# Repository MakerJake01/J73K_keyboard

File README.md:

# J73K_keyboard
a 15*5 ortholinear keyboard using an atmega32a and usb c. V1.1 
with a 3d printed case and all the parts at the top of the pcb. 

Photo [album](https://imgur.com/a/fLlZRP2)
[sound test](https://www.youtube.com/watch?v=JekZULcJLEQ)

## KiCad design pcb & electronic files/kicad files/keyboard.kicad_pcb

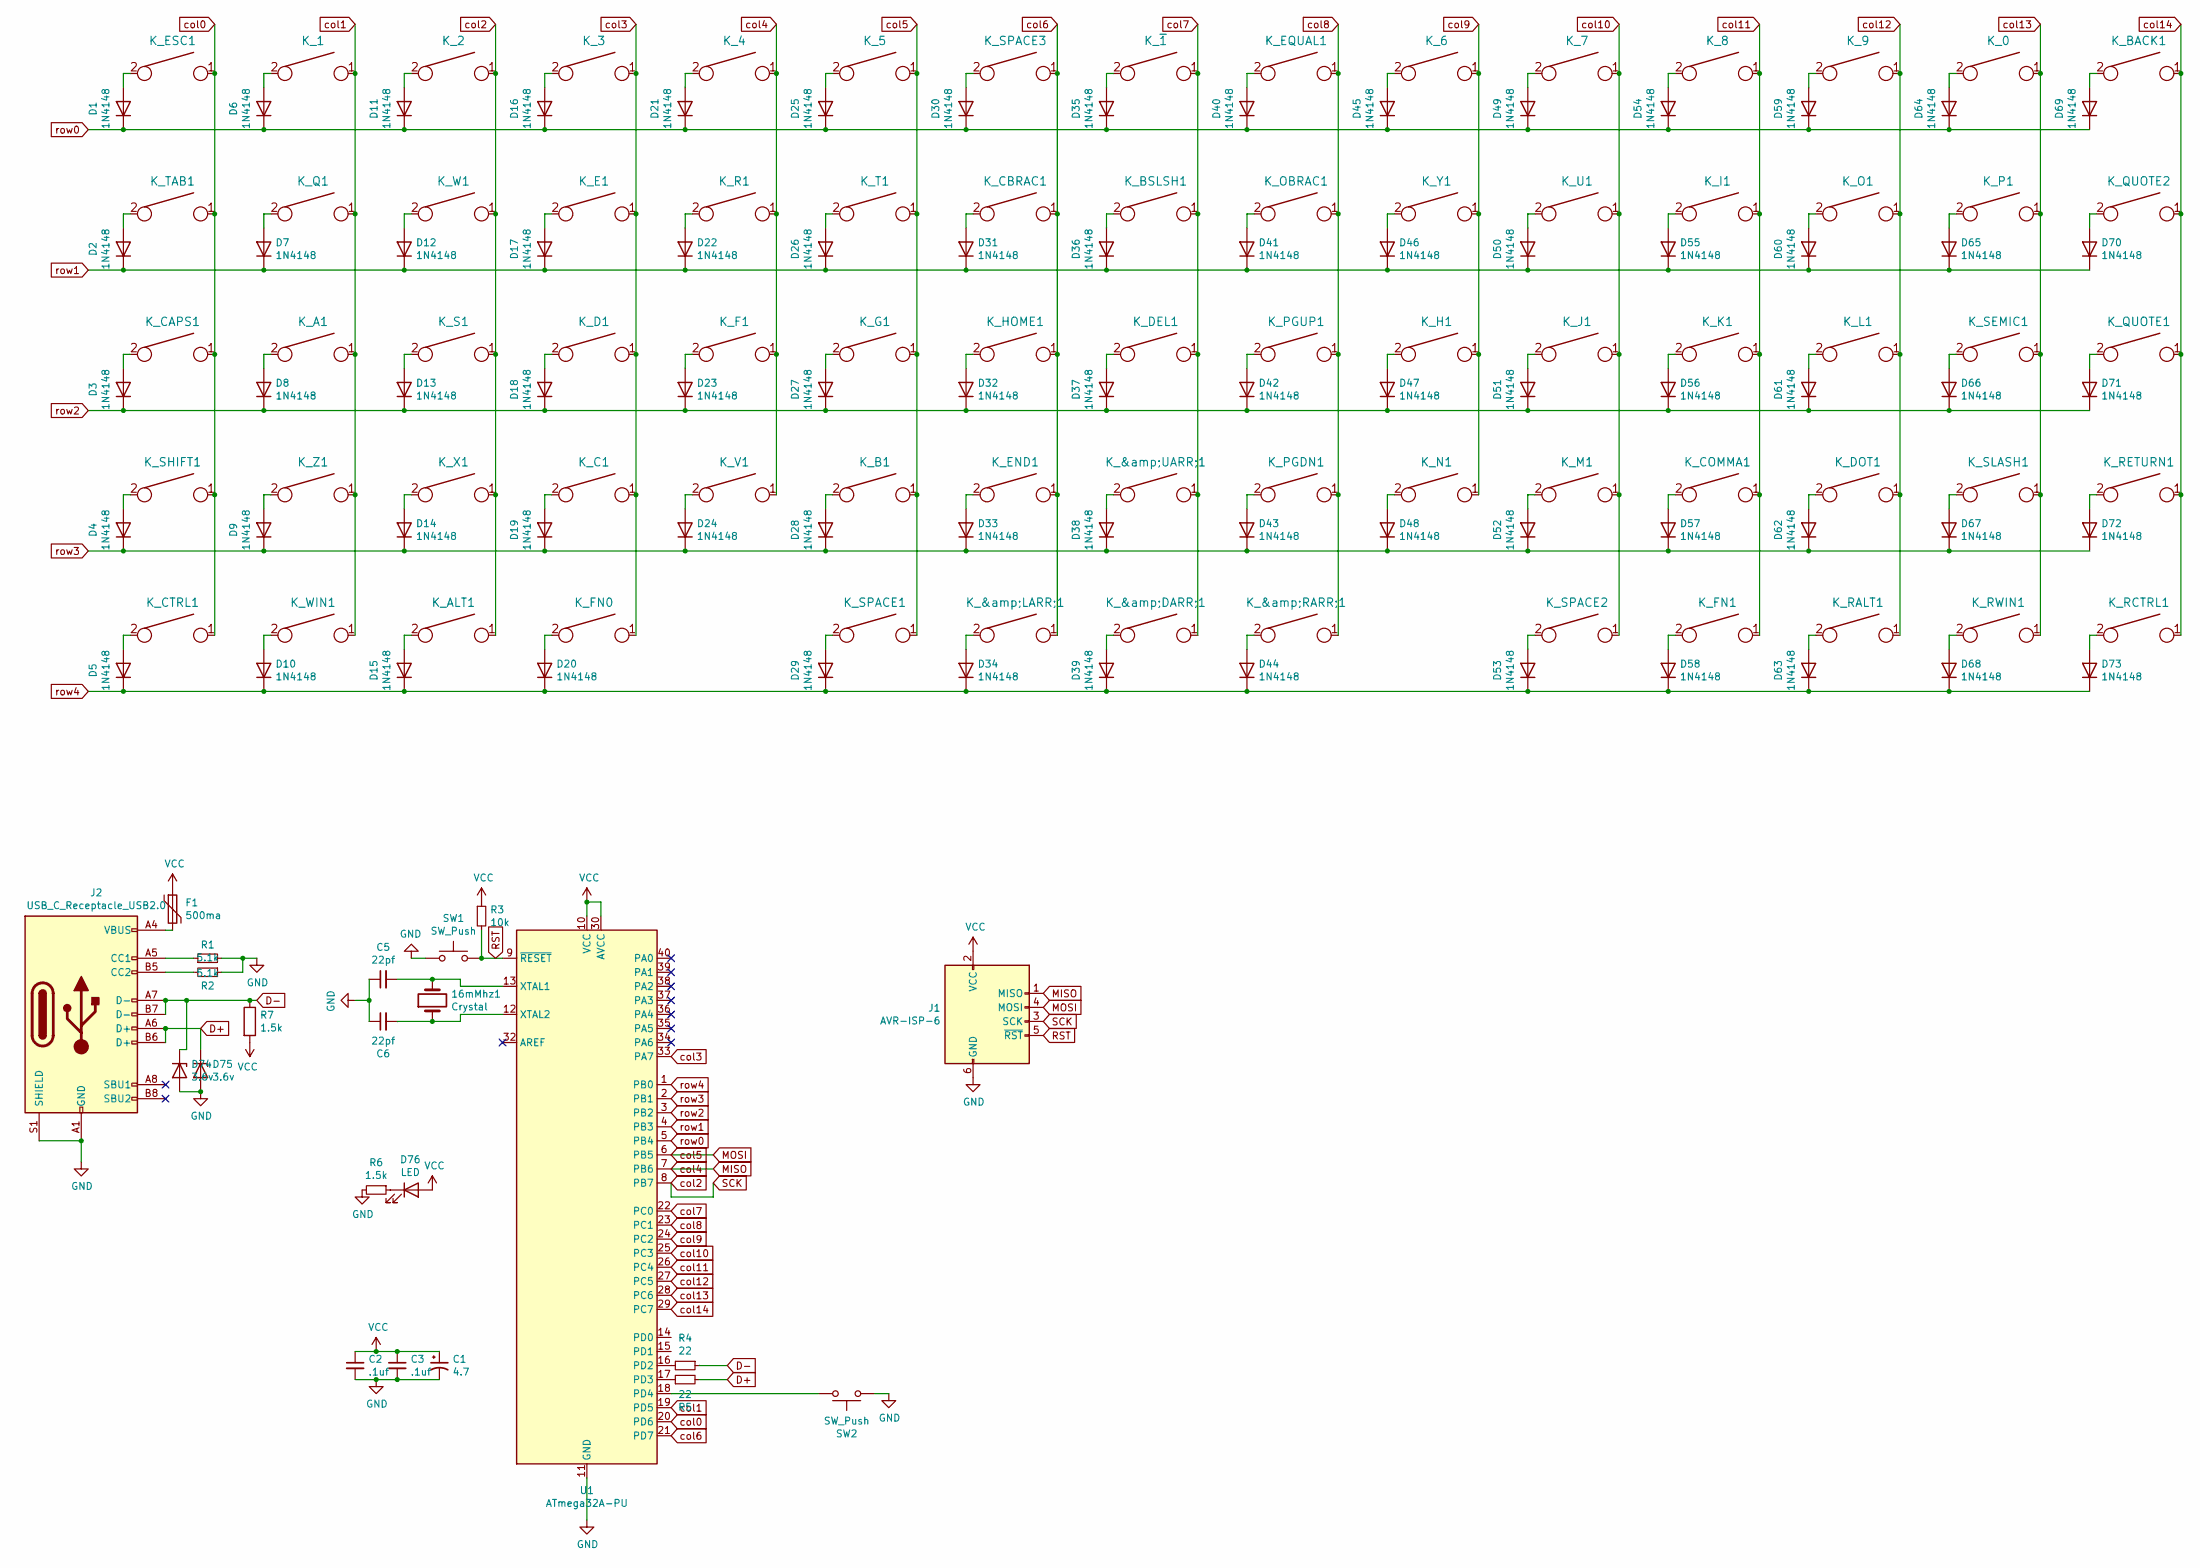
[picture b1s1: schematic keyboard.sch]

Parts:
16mMhz1: Crystal; Crystal_HC49-U_Vertical
C1: 4.7; CP_Radial_D4.0mm_P1.50mm
C2, C3: .1uf; C_Disc_D3.0mm_W1.6mm_P2.50mm
C5, C6: 22pf; C_Disc_D3.0mm_W1.6mm_P2.50mm
D1, D2, D3, D4, D5, D6, D7, D8, D9, D10, D11, D12, D13, D14, D15, D16, D17, D18, D19, D20, D21, D22, D23, D24, D25, D26, D27, D28, D29, D30, D31, D32, D33, D34, D35, D36, D37, D38, D39, D40, D41, D42, D43, D44, D45, D46, D47, D48, D49, D50, D51, D52, D53, D54, D55, D56, D57, D58, D59, D60, D61, D62, D63, D64, D65, D66, D67, D68, D69, D70, D71, D72, D73: 1N4148; D_DO-35_SOD27_P7.62mm_Horizontal
D74, D75: 3.6v; D_DO-35_SOD27_P5.08mm_Horizontal
D76: LED; LED_D3.0mm
F1: 500ma; polyfuse_5.1mm
J1: AVR-ISP-6; AVR_ICSP_3x2
J2: USB_C_Receptacle_USB2.0; USB_C_Receptacle_XKB_U262-16XN-4BVC11
K_0, K_1, K_2, K_3, K_4, K_5, K_6, K_7, K_8, K_9: KEYSW; SW_Cherry_MX_1.00u_PCB
K_&amp;DARR;1: KEYSW; SW_Cherry_MX_1.00u_PCB
K_&amp;LARR;1: KEYSW; SW_Cherry_MX_1.00u_PCB
K_&amp;RARR;1: KEYSW; SW_Cherry_MX_1.00u_PCB
K_&amp;UARR;1: KEYSW; SW_Cherry_MX_1.00u_PCB
K_A1: KEYSW; SW_Cherry_MX_1.00u_PCB
K_ALT1: KEYSW; SW_Cherry_MX_1.00u_PCB
K_B1: KEYSW; SW_Cherry_MX_1.00u_PCB
K_BACK1: KEYSW; SW_Cherry_MX_1.00u_PCB
K_BSLSH1: KEYSW; SW_Cherry_MX_1.00u_PCB
K_C1: KEYSW; SW_Cherry_MX_1.00u_PCB
K_CAPS1: KEYSW; SW_Cherry_MX_1.00u_PCB
K_CBRAC1: KEYSW; SW_Cherry_MX_1.00u_PCB
K_COMMA1: KEYSW; SW_Cherry_MX_1.00u_PCB
K_CTRL1: KEYSW; SW_Cherry_MX_1.00u_PCB
K_D1: KEYSW; SW_Cherry_MX_1.00u_PCB
K_DEL1: KEYSW; SW_Cherry_MX_1.00u_PCB
K_DOT1: KEYSW; SW_Cherry_MX_1.00u_PCB
K_E1: KEYSW; SW_Cherry_MX_1.00u_PCB
K_END1: KEYSW; SW_Cherry_MX_1.00u_PCB
K_EQUAL1: KEYSW; SW_Cherry_MX_1.00u_PCB
K_ESC1: KEYSW; SW_Cherry_MX_1.00u_PCB
K_F1: KEYSW; SW_Cherry_MX_1.00u_PCB
K_FN0, K_FN1: KEYSW; SW_Cherry_MX_1.00u_PCB
K_G1: KEYSW; SW_Cherry_MX_1.00u_PCB
K_H1: KEYSW; SW_Cherry_MX_1.00u_PCB
K_HOME1: KEYSW; SW_Cherry_MX_1.00u_PCB
K_I1: KEYSW; SW_Cherry_MX_1.00u_PCB
K_J1: KEYSW; SW_Cherry_MX_1.00u_PCB
K_K1: KEYSW; SW_Cherry_MX_1.00u_PCB
K_L1: KEYSW; SW_Cherry_MX_1.00u_PCB
K_M1: KEYSW; SW_Cherry_MX_1.00u_PCB
K_N1: KEYSW; SW_Cherry_MX_1.00u_PCB
K_O1: KEYSW; SW_Cherry_MX_1.00u_PCB
K_OBRAC1: KEYSW; SW_Cherry_MX_1.00u_PCB
K_P1: KEYSW; SW_Cherry_MX_1.00u_PCB
K_PGDN1: KEYSW; SW_Cherry_MX_1.00u_PCB
K_PGUP1: KEYSW; SW_Cherry_MX_1.00u_PCB
K_Q1: KEYSW; SW_Cherry_MX_1.00u_PCB
K_QUOTE1, K_QUOTE2: KEYSW; SW_Cherry_MX_1.00u_PCB
K_R1: KEYSW; SW_Cherry_MX_1.00u_PCB
K_RALT1: KEYSW; SW_Cherry_MX_1.00u_PCB
K_RCTRL1: KEYSW; SW_Cherry_MX_1.00u_PCB
K_RETURN1: KEYSW; SW_Cherry_MX_1.00u_PCB
K_RWIN1: KEYSW; SW_Cherry_MX_1.00u_PCB
K_S1: KEYSW; SW_Cherry_MX_1.00u_PCB
K_SEMIC1: KEYSW; SW_Cherry_MX_1.00u_PCB
K_SHIFT1: KEYSW; SW_Cherry_MX_1.00u_PCB
K_SLASH1: KEYSW; SW_Cherry_MX_1.00u_PCB
K_SPACE1, K_SPACE2: KEYSW; SW_Cherry_MX_2.00u_PCB
K_SPACE3: KEYSW; SW_Cherry_MX_1.00u_PCB
K_T1: KEYSW; SW_Cherry_MX_1.00u_PCB
K_TAB1: KEYSW; SW_Cherry_MX_1.00u_PCB
K_U1: KEYSW; SW_Cherry_MX_1.00u_PCB
K_V1: KEYSW; SW_Cherry_MX_1.00u_PCB
K_W1: KEYSW; SW_Cherry_MX_1.00u_PCB
K_WIN1: KEYSW; SW_Cherry_MX_1.00u_PCB
K_X1: KEYSW; SW_Cherry_MX_1.00u_PCB
K_Y1: KEYSW; SW_Cherry_MX_1.00u_PCB
K_Z1: KEYSW; SW_Cherry_MX_1.00u_PCB
K_~1: KEYSW; SW_Cherry_MX_1.00u_PCB
R1, R2: 5.1k; R_Axial_DIN0204_L3.6mm_D1.6mm_P5.08mm_Horizontal
R3: 10k; R_Axial_DIN0204_L3.6mm_D1.6mm_P5.08mm_Horizontal
R4, R5: 22; R_Axial_DIN0204_L3.6mm_D1.6mm_P5.08mm_Horizontal
R6, R7: 1.5k; R_Axial_DIN0204_L3.6mm_D1.6mm_P5.08mm_Horizontal
SW1, SW2: SW_Push; SW_PUSH_6mm
U1: ATmega32A-PU; DIP-40_W15.24mm

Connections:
D+: D75.1 (K), J2.A6 (D+), J2.B6 (D+), R5.2
D-: D74.1 (K), J2.A7 (D-), J2.B7 (D-), R4.1, R7.1
GND: C1.2, C2.2, C3.2, C5.1, C6.1, D74.2 (A), D75.2 (A), J1.6 (GND), J2.A1 (GND), J2.A12 (GND), J2.B1 (GND), J2.B12 (GND), J2.S1 (SHIELD), R1.1, R2.2, R6.2, SW1.1, SW2.1, U1.11 (GND), U1.31 (GND)
MISO: J1.1 (MISO), K_4.1, K_F1.1, K_R1.1, K_V1.1, U1.7 (PB6)
MOSI: J1.4 (MOSI), K_5.1, K_B1.1, K_G1.1, K_SPACE1.1, K_T1.1, U1.6 (PB5)
unnamed: 16mMhz1.1, C6.2, U1.12 (XTAL2)
unnamed: 16mMhz1.2, C5.2, U1.13 (XTAL1)
unnamed: D1.2 (A), K_ESC1.2
unnamed: D2.2 (A), K_TAB1.2
unnamed: D3.2 (A), K_CAPS1.2
unnamed: D4.2 (A), K_SHIFT1.2
unnamed: D5.2 (A), K_CTRL1.2
unnamed: D6.2 (A), K_1.2
unnamed: D7.2 (A), K_Q1.2
unnamed: D8.2 (A), K_A1.2
unnamed: D9.2 (A), K_Z1.2
unnamed: D10.2 (A), K_WIN1.2
unnamed: D11.2 (A), K_2.2
unnamed: D12.2 (A), K_W1.2
unnamed: D13.2 (A), K_S1.2
unnamed: D14.2 (A), K_X1.2
unnamed: D15.2 (A), K_ALT1.2
unnamed: D16.2 (A), K_3.2
unnamed: D17.2 (A), K_E1.2
unnamed: D18.2 (A), K_D1.2
unnamed: D19.2 (A), K_C1.2
unnamed: D20.2 (A), K_FN0.2
unnamed: D21.2 (A), K_4.2
unnamed: D22.2 (A), K_R1.2
unnamed: D23.2 (A), K_F1.2
unnamed: D24.2 (A), K_V1.2
unnamed: D25.2 (A), K_5.2
unnamed: D26.2 (A), K_T1.2
unnamed: D27.2 (A), K_G1.2
unnamed: D28.2 (A), K_B1.2
unnamed: D29.2 (A), K_SPACE1.2
unnamed: D30.2 (A), K_SPACE3.2
unnamed: D31.2 (A), K_CBRAC1.2
unnamed: D32.2 (A), K_HOME1.2
unnamed: D33.2 (A), K_END1.2
unnamed: D34.2 (A), K_&amp;LARR;1.2
unnamed: D35.2 (A), K_~1.2
unnamed: D36.2 (A), K_BSLSH1.2
unnamed: D37.2 (A), K_DEL1.2
unnamed: D38.2 (A), K_&amp;UARR;1.2
unnamed: D39.2 (A), K_&amp;DARR;1.2
unnamed: D40.2 (A), K_EQUAL1.2
unnamed: D41.2 (A), K_OBRAC1.2
unnamed: D42.2 (A), K_PGUP1.2
unnamed: D43.2 (A), K_PGDN1.2
unnamed: D44.2 (A), K_&amp;RARR;1.2
unnamed: D45.2 (A), K_6.2
unnamed: D46.2 (A), K_Y1.2
unnamed: D47.2 (A), K_H1.2
unnamed: D48.2 (A), K_N1.2
unnamed: D49.2 (A), K_7.2
unnamed: D50.2 (A), K_U1.2
unnamed: D51.2 (A), K_J1.2
unnamed: D52.2 (A), K_M1.2
unnamed: D53.2 (A), K_SPACE2.2
unnamed: D54.2 (A), K_8.2
unnamed: D55.2 (A), K_I1.2
unnamed: D56.2 (A), K_K1.2
unnamed: D57.2 (A), K_COMMA1.2
unnamed: D58.2 (A), K_FN1.2
unnamed: D59.2 (A), K_9.2
unnamed: D60.2 (A), K_O1.2
unnamed: D61.2 (A), K_L1.2
unnamed: D62.2 (A), K_DOT1.2
unnamed: D63.2 (A), K_RALT1.2
unnamed: D64.2 (A), K_0.2
unnamed: D65.2 (A), K_P1.2
unnamed: D66.2 (A), K_SEMIC1.2
unnamed: D67.2 (A), K_SLASH1.2
unnamed: D68.2 (A), K_RWIN1.2
unnamed: D69.2 (A), K_BACK1.2
unnamed: D70.2 (A), K_QUOTE2.2
unnamed: D71.2 (A), K_QUOTE1.2
unnamed: D72.2 (A), K_RETURN1.2
unnamed: D73.2 (A), K_RCTRL1.2
unnamed: D76.1 (K), R6.1
unnamed: F1.2, J2.A4 (VBUS), J2.A9 (VBUS), J2.B4 (VBUS), J2.B9 (VBUS)
unnamed: J2.A5 (CC1), R2.1
unnamed: J2.B5 (CC2), R1.2
unnamed: R4.2, U1.16 (PD2)
unnamed: R5.1, U1.17 (PD3)
unnamed: SW2.2, U1.18 (PD4)
RST: J1.5 (~RST), R3.2, SW1.2, U1.9 (~RESET)
SCK: J1.3 (SCK), K_2.1, K_ALT1.1, K_S1.1, K_W1.1, K_X1.1, U1.8 (PB7)
VCC: C1.1, C2.1, C3.1, D76.2 (A), F1.1, J1.2 (VCC), R3.1, R7.2, U1.10 (VCC), U1.30 (AVCC)
col0: K_CAPS1.1, K_CTRL1.1, K_ESC1.1, K_SHIFT1.1, K_TAB1.1, U1.20 (PD6)
col1: K_1.1, K_A1.1, K_Q1.1, K_WIN1.1, K_Z1.1, U1.19 (PD5)
col3: K_3.1, K_C1.1, K_D1.1, K_E1.1, K_FN0.1, U1.33 (PA7)
col6: K_&amp;LARR;1.1, K_CBRAC1.1, K_END1.1, K_HOME1.1, K_SPACE3.1, U1.21 (PD7)
col7: K_&amp;DARR;1.1, K_&amp;UARR;1.1, K_BSLSH1.1, K_DEL1.1, K_~1.1, U1.22 (PC0)
col8: K_&amp;RARR;1.1, K_EQUAL1.1, K_OBRAC1.1, K_PGDN1.1, K_PGUP1.1, U1.23 (PC1)
col9: K_6.1, K_H1.1, K_N1.1, K_Y1.1, U1.24 (PC2)
col10: K_7.1, K_J1.1, K_M1.1, K_SPACE2.1, K_U1.1, U1.25 (PC3)
col11: K_8.1, K_COMMA1.1, K_FN1.1, K_I1.1, K_K1.1, U1.26 (PC4)
col12: K_9.1, K_DOT1.1, K_L1.1, K_O1.1, K_RALT1.1, U1.27 (PC5)
col13: K_0.1, K_P1.1, K_RWIN1.1, K_SEMIC1.1, K_SLASH1.1, U1.28 (PC6)
col14: K_BACK1.1, K_QUOTE1.1, K_QUOTE2.1, K_RCTRL1.1, K_RETURN1.1, U1.29 (PC7)
row0: D1.1 (K), D6.1 (K), D11.1 (K), D16.1 (K), D21.1 (K), D25.1 (K), D30.1 (K), D35.1 (K), D40.1 (K), D45.1 (K), D49.1 (K), D54.1 (K), D59.1 (K), D64.1 (K), D69.1 (K), U1.5 (PB4)
row1: D2.1 (K), D7.1 (K), D12.1 (K), D17.1 (K), D22.1 (K), D26.1 (K), D31.1 (K), D36.1 (K), D41.1 (K), D46.1 (K), D50.1 (K), D55.1 (K), D60.1 (K), D65.1 (K), D70.1 (K), U1.4 (PB3)
row2: D3.1 (K), D8.1 (K), D13.1 (K), D18.1 (K), D23.1 (K), D27.1 (K), D32.1 (K), D37.1 (K), D42.1 (K), D47.1 (K), D51.1 (K), D56.1 (K), D61.1 (K), D66.1 (K), D71.1 (K), U1.3 (PB2)
row3: D4.1 (K), D9.1 (K), D14.1 (K), D19.1 (K), D24.1 (K), D28.1 (K), D33.1 (K), D38.1 (K), D43.1 (K), D48.1 (K), D52.1 (K), D57.1 (K), D62.1 (K), D67.1 (K), D72.1 (K), U1.2 (PB1)
row4: D5.1 (K), D10.1 (K), D15.1 (K), D20.1 (K), D29.1 (K), D34.1 (K), D39.1 (K), D44.1 (K), D53.1 (K), D58.1 (K), D63.1 (K), D68.1 (K), D73.1 (K), U1.1 (PB0)

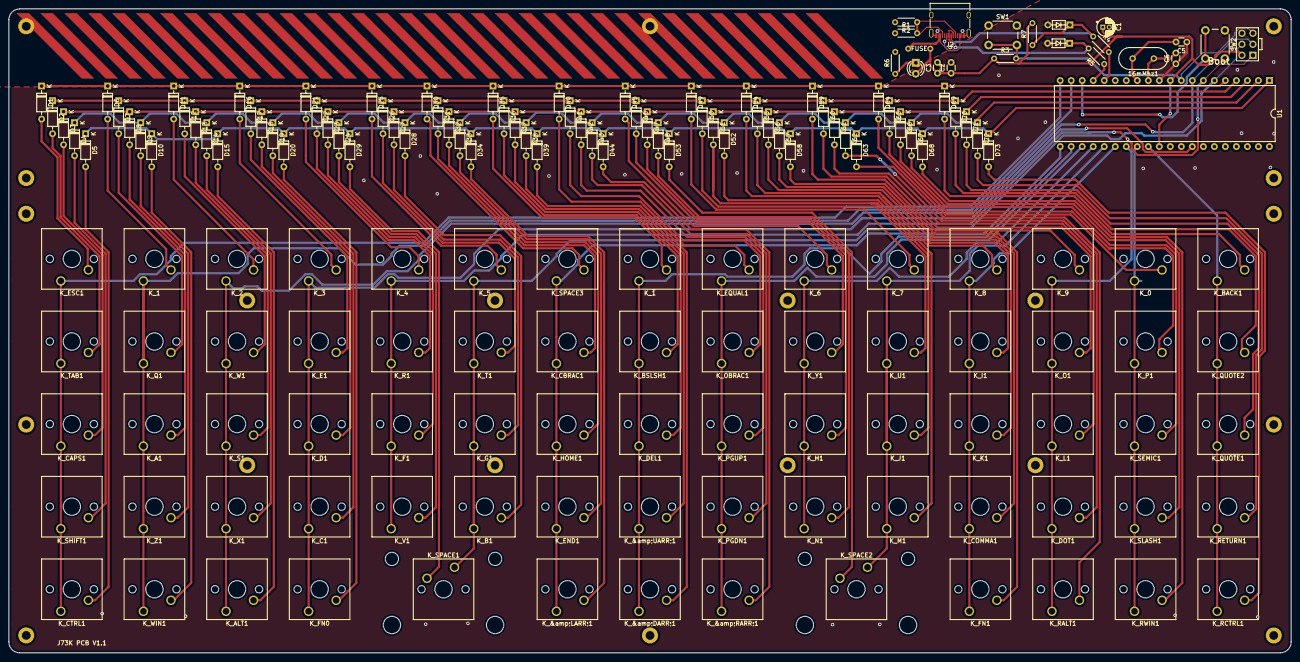
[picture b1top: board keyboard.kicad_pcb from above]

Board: 2 copper layers, 295.8 x 148.5 mm, 188 parts (0 on the bottom side), 107 nets.

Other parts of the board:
P?: CONN_1; PIN_1
P?#2, P?#3, P?#4, P?#5, P?#6, P?#7, P?#8, P?#9, P?#10, P?#11, P?#12, P?#13, P?#14, P?#15, P?#16, P?#17, P?#18, P?#19, P?#20: CONN_1; PIN_1

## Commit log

2021-02-01 added qmk files
    keymap and other files
2021-02-01 added mostly all the files
2021-02-01 changed the pcb
    changes some of the files
